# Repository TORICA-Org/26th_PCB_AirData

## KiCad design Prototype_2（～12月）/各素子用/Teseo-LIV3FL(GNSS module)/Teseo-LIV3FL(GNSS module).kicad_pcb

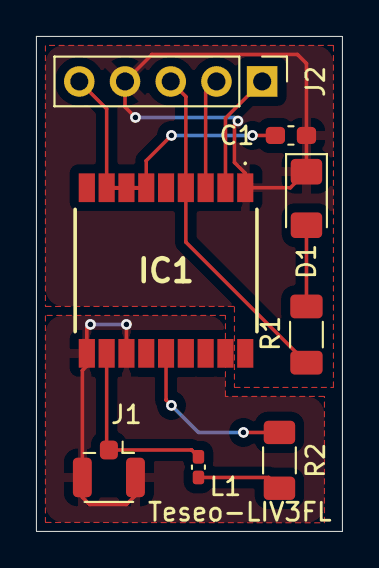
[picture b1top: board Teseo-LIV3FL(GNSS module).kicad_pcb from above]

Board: 2 copper layers, 17.0 x 27.5 mm, 8 parts (0 on the bottom side), 10 nets.

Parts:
C1: 0.1u; C_0603_1608Metric_Pad1.08x0.95mm_HandSolder
D1: LED; LED_1206_3216Metric_Pad1.42x1.75mm_HandSolder
IC1: TESEO-LIV3FL; TESEOLIV3FL
J1: Conn_Coaxial; U.FL_Hirose_U.FL-R-SMT-1_Vertical
J2: Conn_01x05_Pin; PinHeader_1x05_P2.54mm_Vertical
L1: 27nH; L_0402_1005Metric_Pad0.77x0.64mm_HandSolder
R1: 200Ω; C_1206_3216Metric_Pad1.33x1.80mm_HandSolder
R2: 10Ω; R_1206_3216Metric_Pad1.30x1.75mm_HandSolder

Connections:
+3V3: C1.1, IC1.6 (VBATT), IC1.7 (VCC_IO), IC1.8 (VCC), J2.5
GND: C1.2, D1.1 (K), IC1.1 (GND), J2.4
GND1: IC1.10 (GND_RF_1), IC1.12 (GND_RF_2), J1.2 (Ext)
unnamed: D1.2 (A), R1.2
unnamed: IC1.4 (1PPS), J2.3, R1.1
unnamed: IC1.11 (RF_IN), J1.1 (In), L1.1
unnamed: IC1.3 (RX), J2.2
unnamed: IC1.2 (TX), J2.1
unnamed: IC1.14 (VCC_RF), R2.2
unnamed: L1.2, R2.1

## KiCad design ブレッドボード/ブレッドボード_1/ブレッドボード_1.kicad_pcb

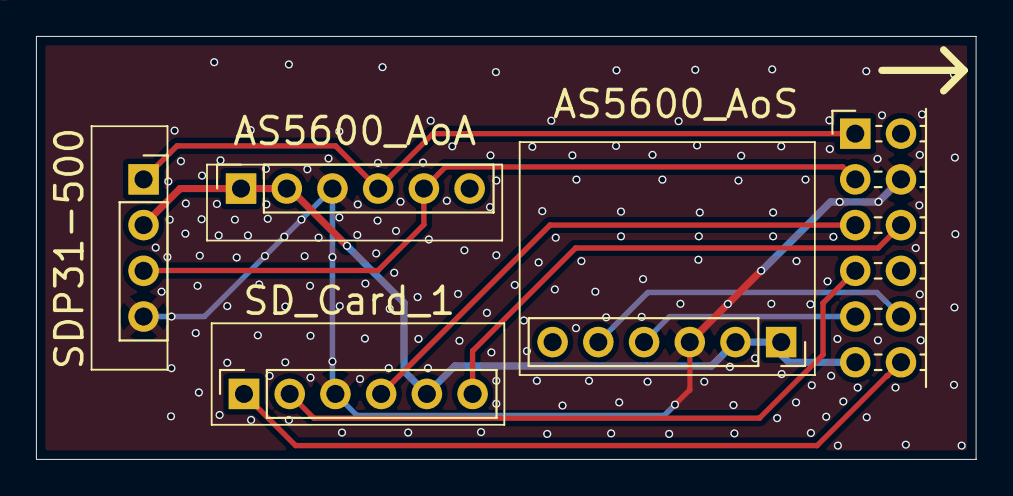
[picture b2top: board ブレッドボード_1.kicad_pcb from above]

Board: 2 copper layers, 52.2 x 23.5 mm, 5 parts (0 on the bottom side), 10 nets.

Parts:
J1: SDP31-500; PinSocket_1x04_P2.54mm_Vertical
J2: AS5600_1; PinSocket_1x06_P2.54mm_Vertical
J3: SD_1; PinSocket_1x06_P2.54mm_Vertical
J4: AS5600_0; PinSocket_1x06_P2.54mm_Vertical
J5: Conn_01x12_Socket; PinHeader_2x06_P2.54mm_Horizontal

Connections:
/3V3_AS0: J1.2, J2.1, J2.2, J3.5, J4.1, J4.2, J5.11
/CLK_SD1: J3.4, J5.5
/CS_SD1: J3.1, J5.12
/DC_GND: J1.4, J2.3, J3.3, J4.3, J5.4
/MISO_SD1: J3.6, J5.6
/MOSI_SD1: J3.2, J5.7
/SCL_AS0: J4.4, J5.9
/SCL_AS1: J1.1, J2.4, J5.1
/SDA_AS0: J4.5, J5.10
/SDA_AS1: J1.3, J2.5, J5.3

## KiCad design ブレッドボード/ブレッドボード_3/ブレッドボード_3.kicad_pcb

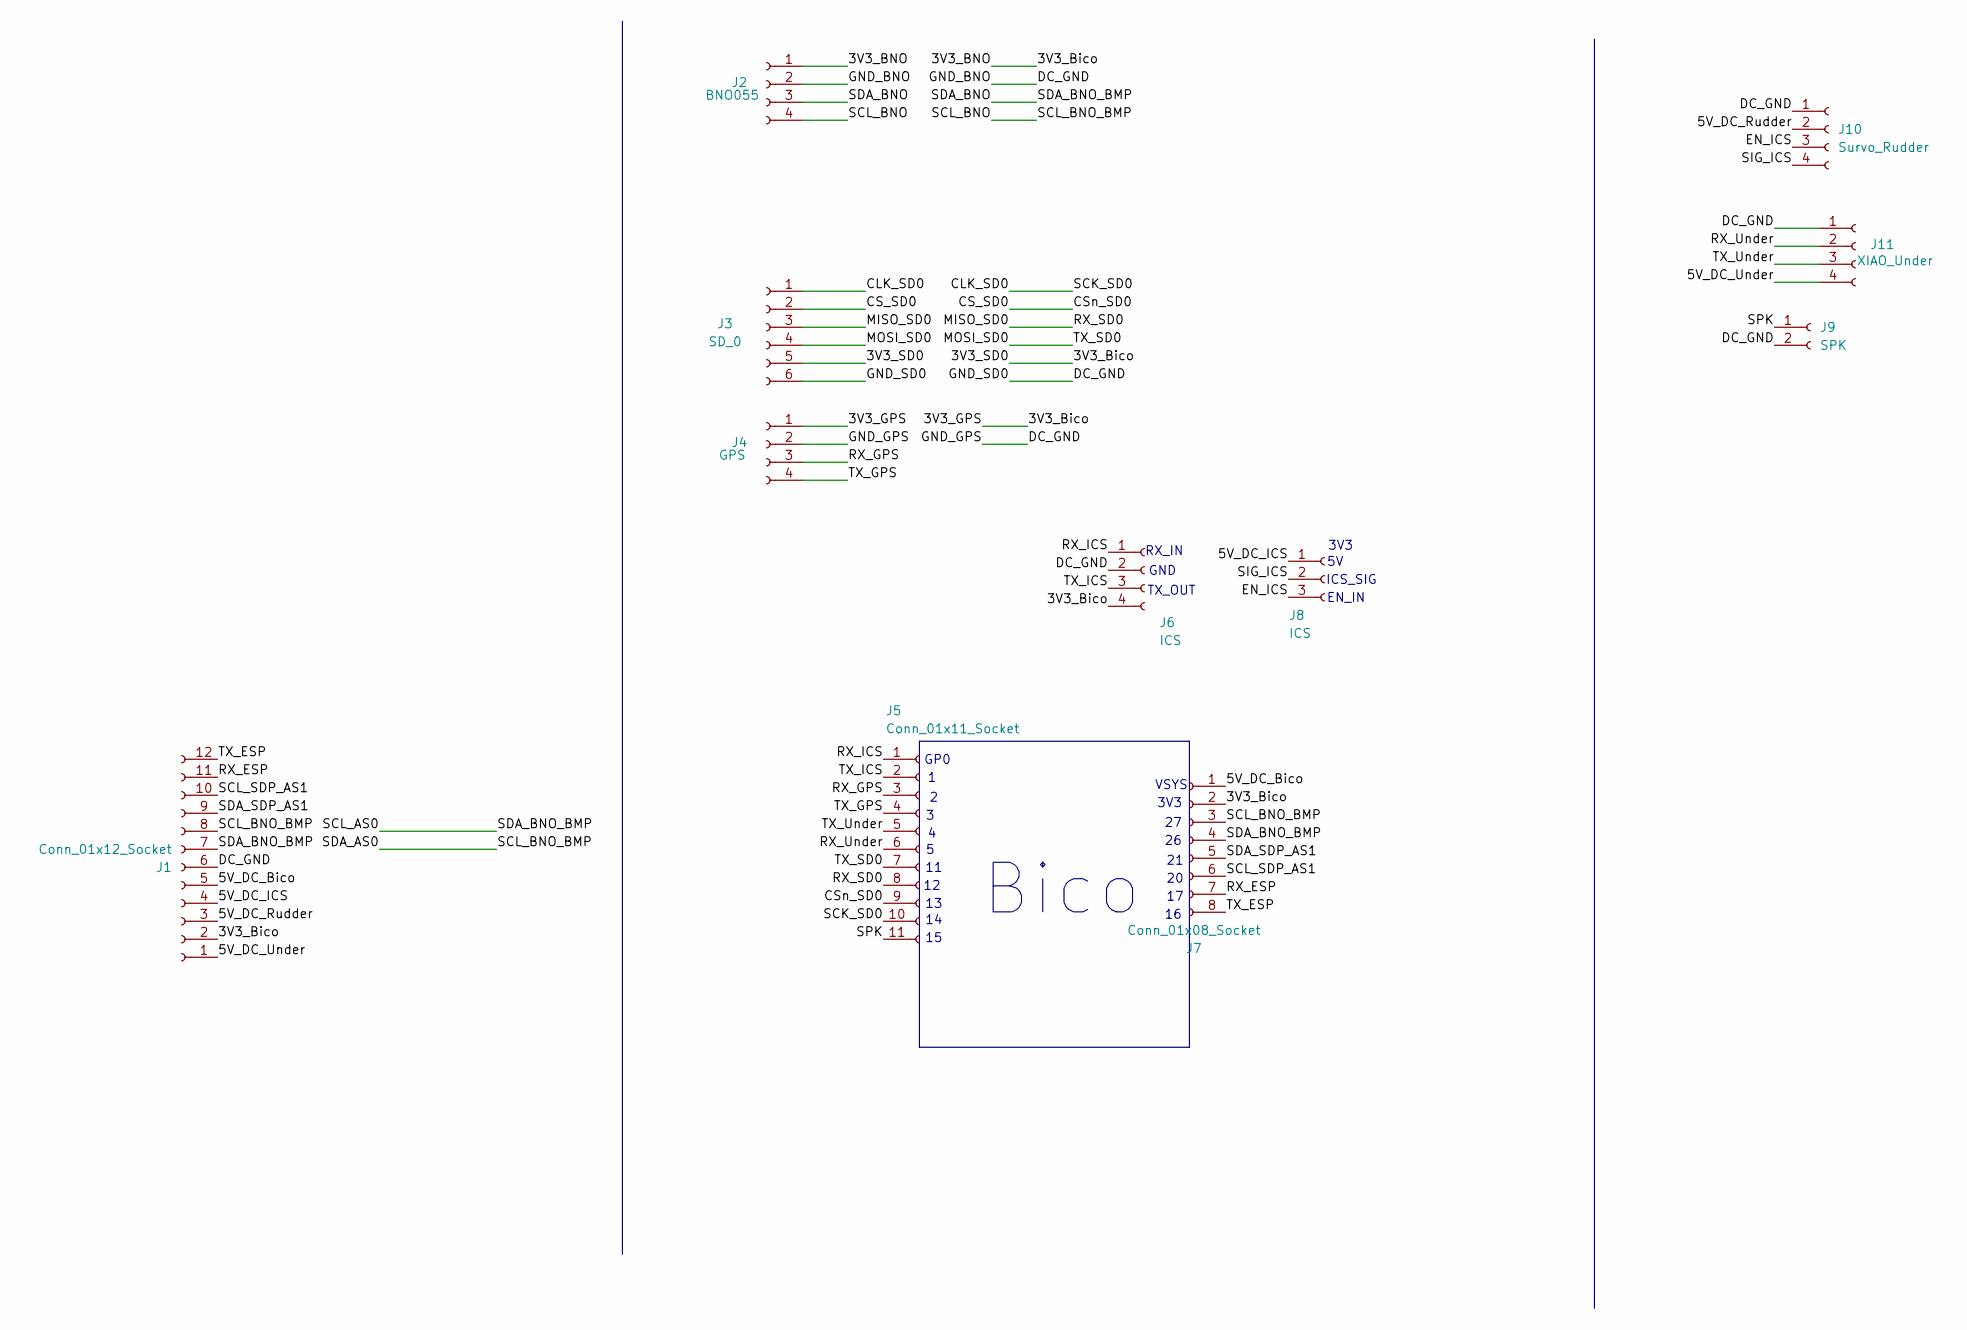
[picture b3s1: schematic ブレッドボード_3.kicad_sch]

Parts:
J1: Conn_01x12_Socket; PinHeader_2x06_P2.54mm_Horizontal
J2: BNO055; PinSocket_1x04_P2.54mm_Vertical
J3: SD_0; PinSocket_1x06_P2.54mm_Vertical
J4: GPS; PinSocket_1x04_P2.54mm_Vertical
J5: Conn_01x11_Socket; PinSocket_1x11_P2.54mm_Vertical
J6: ICS; PinSocket_1x04_P2.54mm_Vertical
J7: Conn_01x08_Socket; PinSocket_1x08_P2.54mm_Vertical
J8: ICS; PinSocket_1x03_P2.54mm_Vertical
J9: SPK; PA_Connector_Post_2Pin
J10: Survo_Rudder; PA_Connector_Pos_4Pin
J11: XIAO_Under; PA_Connector_Pos_4Pin

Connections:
/3V3_BNO: J1.2, J2.1, J3.5, J4.1, J6.4, J7.2
/5V_DC_Bico: J1.5, J7.1
/5V_DC_ICS: J1.4, J8.1
/5V_DC_Rudder: J1.3, J10.2
/5V_DC_Under: J1.1, J11.4
/CLK_SD0: J3.1, J5.10
/CS_SD0: J3.2, J5.9
/DC_GND: J1.6, J2.2, J3.6, J4.2, J6.2, J9.2, J10.1, J11.1
/EN_ICS: J8.3, J10.3
/MISO_SD0: J3.3, J5.8
/MOSI_SD0: J3.4, J5.7
/RX_ESP: J1.11, J7.7
/RX_GPS: J4.3, J5.3
/RX_ICS: J5.1, J6.1
/RX_Under: J5.6, J11.2
/SCL_AS0: J1.7, J2.3, J7.4
/SCL_BNO: J1.8, J2.4, J7.3
/SCL_SDP_AS1: J1.10, J7.6
/SDA_SDP_AS1: J1.9, J7.5
/SIG_ICS: J8.2, J10.4
/SPK: J5.11, J9.1
/TX_ESP: J1.12, J7.8
/TX_GPS: J4.4, J5.4
/TX_ICS: J5.2, J6.3
/TX_Under: J5.5, J11.3

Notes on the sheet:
GP0
3V3
TX_OUT
EN_IN
GND
VSYS
RX_IN
Bico
ICS_SIG

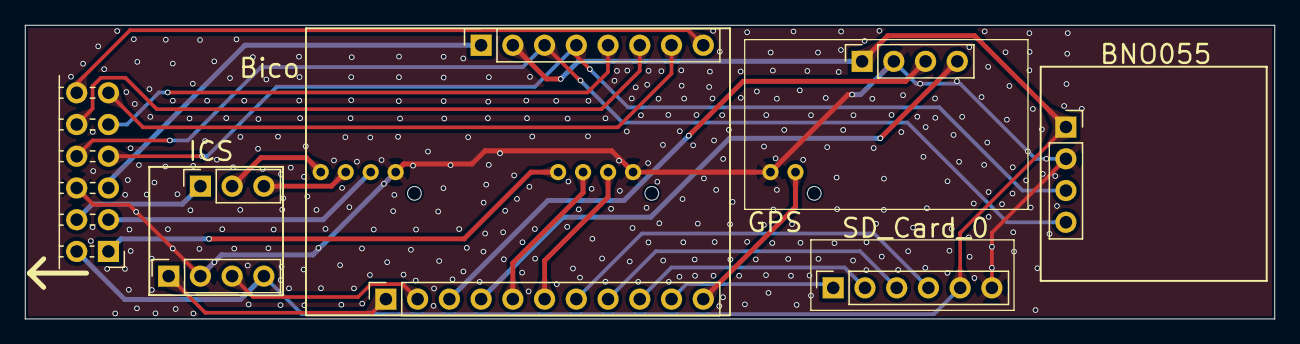
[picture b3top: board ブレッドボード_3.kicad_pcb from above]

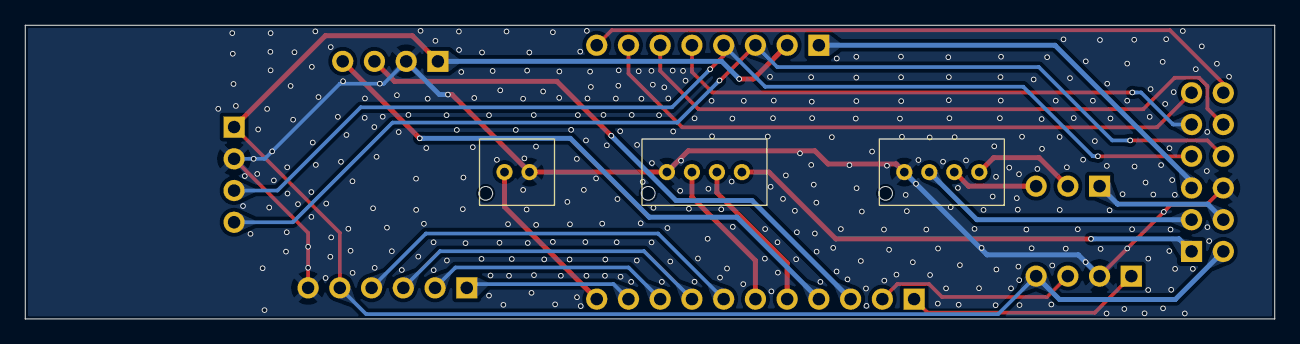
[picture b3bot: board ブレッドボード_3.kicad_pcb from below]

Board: 2 copper layers, 100.0 x 23.5 mm, 11 parts (3 on the bottom side), 25 nets.

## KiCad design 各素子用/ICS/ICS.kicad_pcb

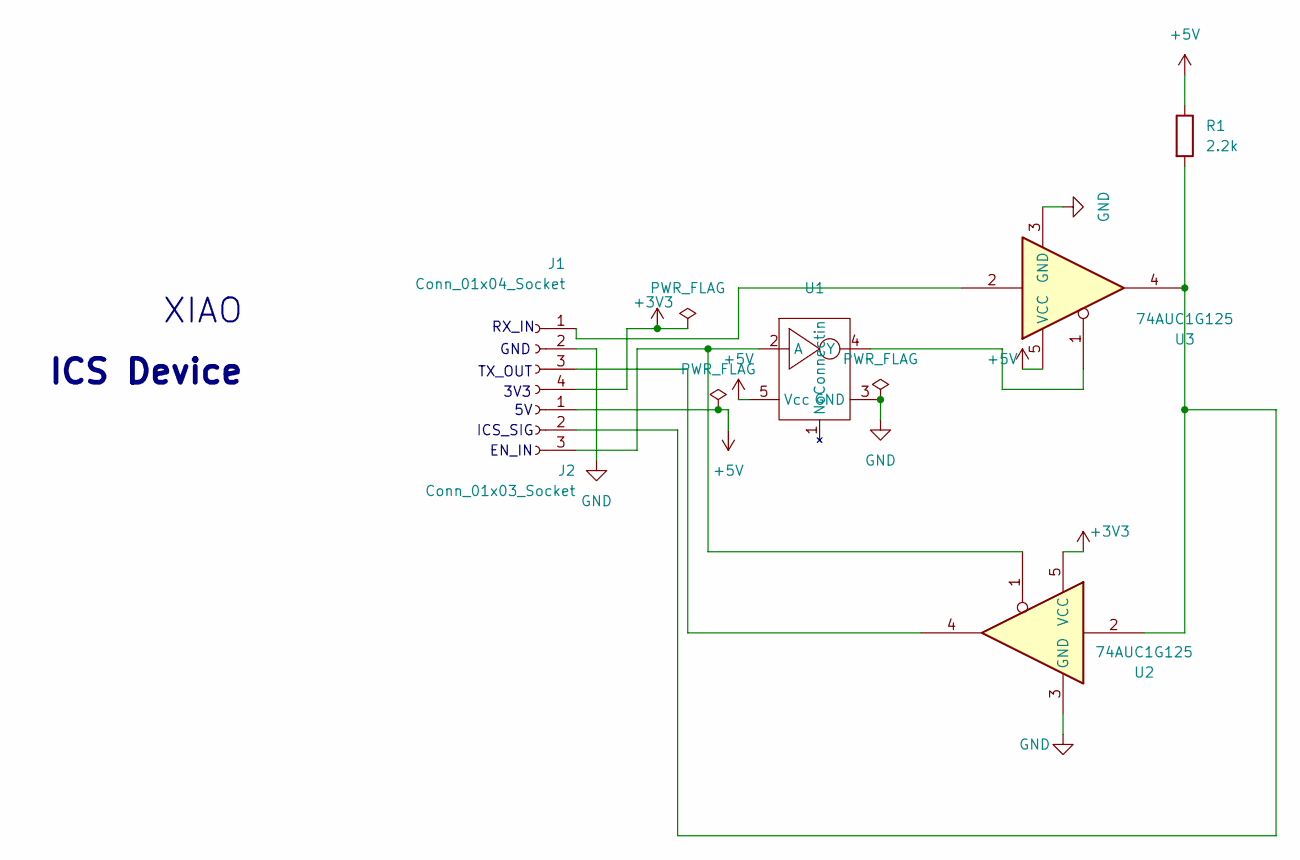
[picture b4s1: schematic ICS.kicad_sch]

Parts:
J1: Conn_01x04_Socket; PinHeader_1x04_P2.54mm_Vertical
J2: Conn_01x03_Socket; PinHeader_1x03_P2.54mm_Vertical
R1: 2.2k; R_0805_2012Metric
U1: 74AHC1G04W5
U2, U3: 74AUC1G125; 74AHC1G04W5

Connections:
+3V3: J1.4, U2.5 (VCC)
+5V: J2.1, R1.1, U1.5 (Vcc), U3.5 (VCC)
GND: J1.2, U1.3 (GND), U2.3 (GND), U3.3 (GND)
unnamed: J1.1, U3.2
unnamed: J1.3, U2.4
unnamed: J2.2, R1.2, U2.2, U3.4
unnamed: J2.3, U1.2 (A), U2.1
unnamed: U1.4 (Y), U3.1

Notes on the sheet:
TX_OUT
EN_IN
GND
RX_IN
ICS_SIG
ICS Device
3V3
XIAO

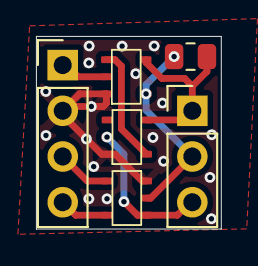
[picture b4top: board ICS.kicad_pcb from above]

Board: 2 copper layers, 10.3 x 10.7 mm, 6 parts (0 on the bottom side), 8 nets.

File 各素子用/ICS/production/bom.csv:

Designator,Footprint,Quantity,Value,LCSC Part #
J1,PinHeader_1x04_P2.54mm_Vertical,1,Conn_01x04_Socket,
J2,PinHeader_1x03_P2.54mm_Vertical,1,Conn_01x03_Socket,
R1,0805,1,2.2k,
U1,74AHC1G04W5,1,~,
"U2, U3",74AHC1G04W5,2,74AUC1G125,
